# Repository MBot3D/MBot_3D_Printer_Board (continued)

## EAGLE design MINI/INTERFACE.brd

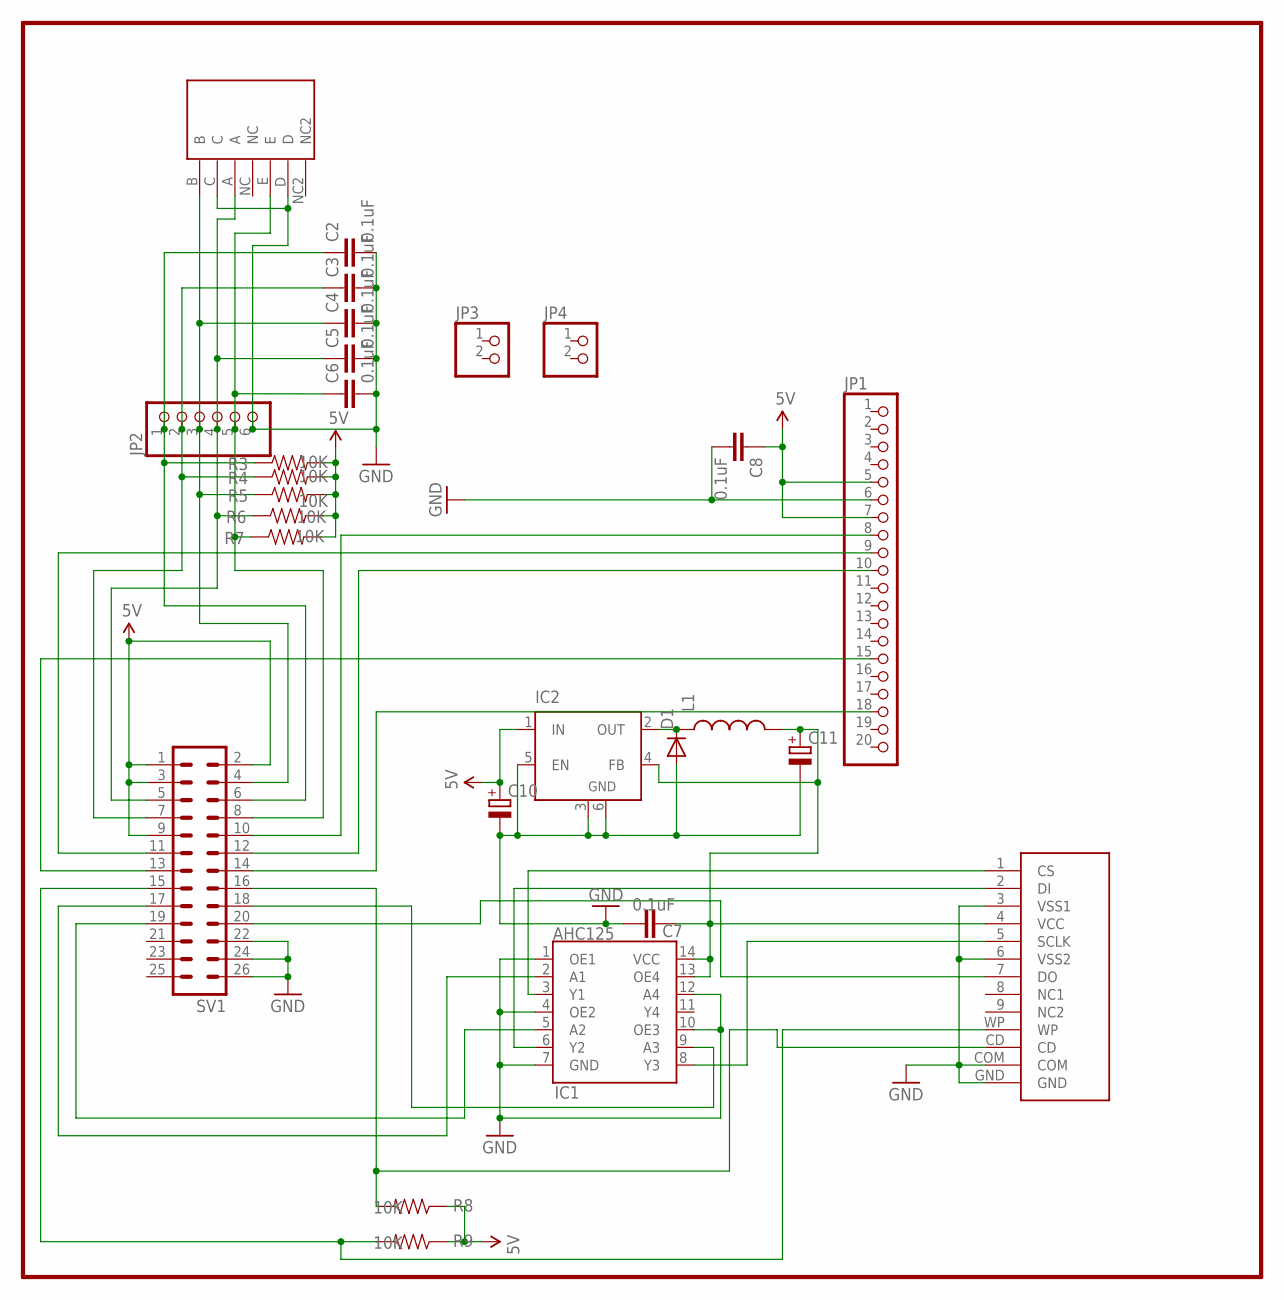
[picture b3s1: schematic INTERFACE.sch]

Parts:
C2, C3, C4, C5, C6, C7, C8: 0.1uF; 0805
C10, C11: CPOL-EUE3.5-8; E3,5-8
D1: DIODESMB; SMB-DIODE
IC1: AHC125; DIN14
IC2: LM2596S; TO263-5
JP1: PINHD-1X20; 1X20
JP2: PINHD-1X6; 1X06
JP3, JP4: PINHD-1X2; 1X02
L1: INDUCTORPWR; CDRH125
Q2: SDCARD
R3, R4, R5, R6, R7, R8, R9: 10K; 0805
S2: DJFS; PIN5
SV1: ML26

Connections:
5V: C8.1, C10.+, IC2.1 (IN), JP1.5, JP1.7, R3.2, R4.2, R5.2, R6.2, R7.2, R8.1, R9.1, SV1.1, SV1.2, SV1.3, SV1.9
GND2: C2.2, C3.2, C4.2, C5.2, C6.2, C7.2, C8.2, C10.-, C11.-, D1.A, IC1.1 (OE1), IC1.4 (OE2), IC1.7 (GND), IC1.10 (OE3), IC1.12 (A4), IC2.3 (GND), IC2.5 (EN), IC2.6 (GND), JP1.6, JP2.6, Q2.3 (VSS1), Q2.6 (VSS2), Q2.COM, Q2.GND, S2.C, S2.D, SV1.22, SV1.24, SV1.26
unnamed: D1.C, IC2.2 (OUT), L1.1
unnamed: IC1.3 (Y1), Q2.1 (CS)
unnamed: C2.1, JP2.1, R3.1, SV1.6
unnamed: IC1.2 (A1), SV1.17
unnamed: IC1.6 (Y2), Q2.2 (DI)
unnamed: Q2.CD, R8.2, SV1.16
unnamed: Q2.7 (DO), SV1.20
unnamed: JP1.15, SV1.13
unnamed: JP1.8, SV1.10
unnamed: JP1.10, SV1.12
unnamed: JP1.9, SV1.11
unnamed: JP1.18, SV1.14
unnamed: IC1.8 (Y3), Q2.5 (SCLK)
unnamed: C3.1, JP2.2, R4.1, SV1.7
unnamed: C4.1, JP2.3, R5.1, S2.B, SV1.4
unnamed: C5.1, JP2.4, R6.1, S2.A, SV1.5
unnamed: C6.1, JP2.5, R7.1, S2.E, SV1.8
unnamed: Q2.WP, R9.2, SV1.15
unnamed: IC1.5 (A2), SV1.19
unnamed: C7.1, C11.+, IC1.13 (OE4), IC1.14 (VCC), IC2.4 (FB), L1.2, Q2.4 (VCC)
unnamed: IC1.9 (A3), SV1.18

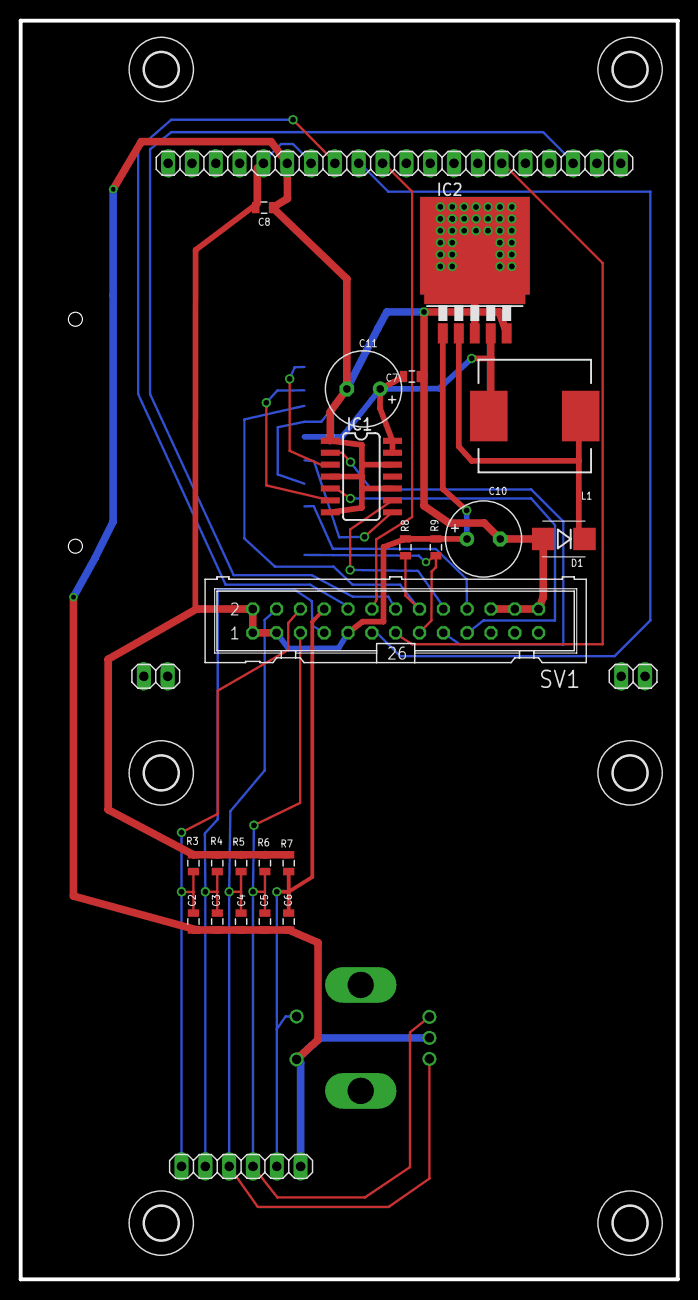
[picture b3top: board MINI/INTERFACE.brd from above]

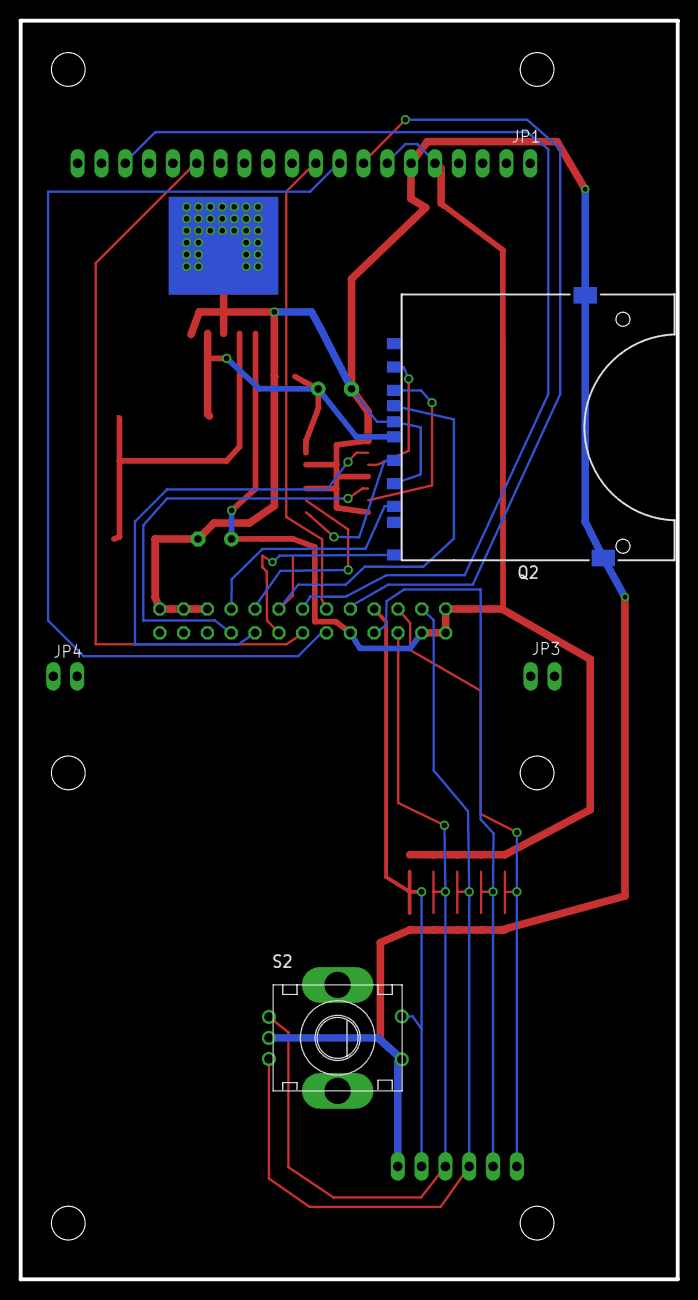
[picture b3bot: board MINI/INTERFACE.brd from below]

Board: 2 copper layers, 70.1 x 134.2 mm, 33 parts (2 on the bottom side), 23 nets.

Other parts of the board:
U$7, U$9, U$14, U$15, U$16, U$17: 3,6

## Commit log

2015-03-09 initial version for grid2+ and mini
